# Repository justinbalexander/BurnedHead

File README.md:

# BurnedHead

A handheld, portable video game system designed with Kicad and programmed in C.

# Description

The processor is the STM32F767ZG, a Cortex-M7 processor selected for the ample
size of the instruction and data caches.  Currently at the board bring-up stage,
the functionality includes an RGB parallel interface, an MMC card socket, a 32MB
SDRAM clocked at 108MHz, D-pad, 4 front facing buttons, 2 shoulder buttons, 2
joysticks, and a speaker. The device is powered through a Micro-USB connector or
a rechargeable LiPo battery for portability.

The final product will load user-selectable ELF files off of the MMC compatible
card into the external RAM and run them as a process.

The project originally began in Zig but is transitioning to C to reduce
friction when integrating with libraries and vendor code and to allow progress
without requiring fiddling with a language still in beta.

# Building

## Cloning the Repository

This repository uses submodules to manage dependencies.

```bash
git clone --recurse-submodules https://github.com/vegecode/BurnedHead.git
```

## Building the Application

BurnedHead uses Makefiles.
Navigate to the base directory of the clone, and
point to the specific Makefile you want to build (currently only one):

Example:

```bash
make -f configurations/${CONFIGURATION_NAME}/Makefile
```

The resulting executable(s) are in `./build/${CONFIGURATION_NAME}`

# Debugging on the Target

Debugging is done using GDB in a shell with the JLink GDBServer providing the
connection to the remote target.

Running the shell script `./debug/start_debug /path/to/elf_file` will start the
GDBServer and connect GDB to it, then a gdb script loads the executable and sets
a temporary breakpoint at the reset handler.

A sample of some external RAM tests during board bring-up in a Vim/GDB session:

Another easy alternative if you are using a JLink debug probe is to use Ozone,
the standalone debugger from Segger or Segger Embedded Workbench which are
both free to use for non-commercial purposes.

Integrating with Eclipse should also be possible using the MCU GNU Eclipse
plugins.

# Hand-Assembled Revision 0 Board

The back of the first revision of the board was assembled using solder paste and
a cast-iron skillet over a stand-alone burner for reflow. Some rework was
required as applying the paste without a stencil resulted in uneven application.
The front side components were hand soldered.

# Renders

# Attributions

Some symbols and footprints  came from www.snapeda.com. See the library folder for the required
license and attributions.

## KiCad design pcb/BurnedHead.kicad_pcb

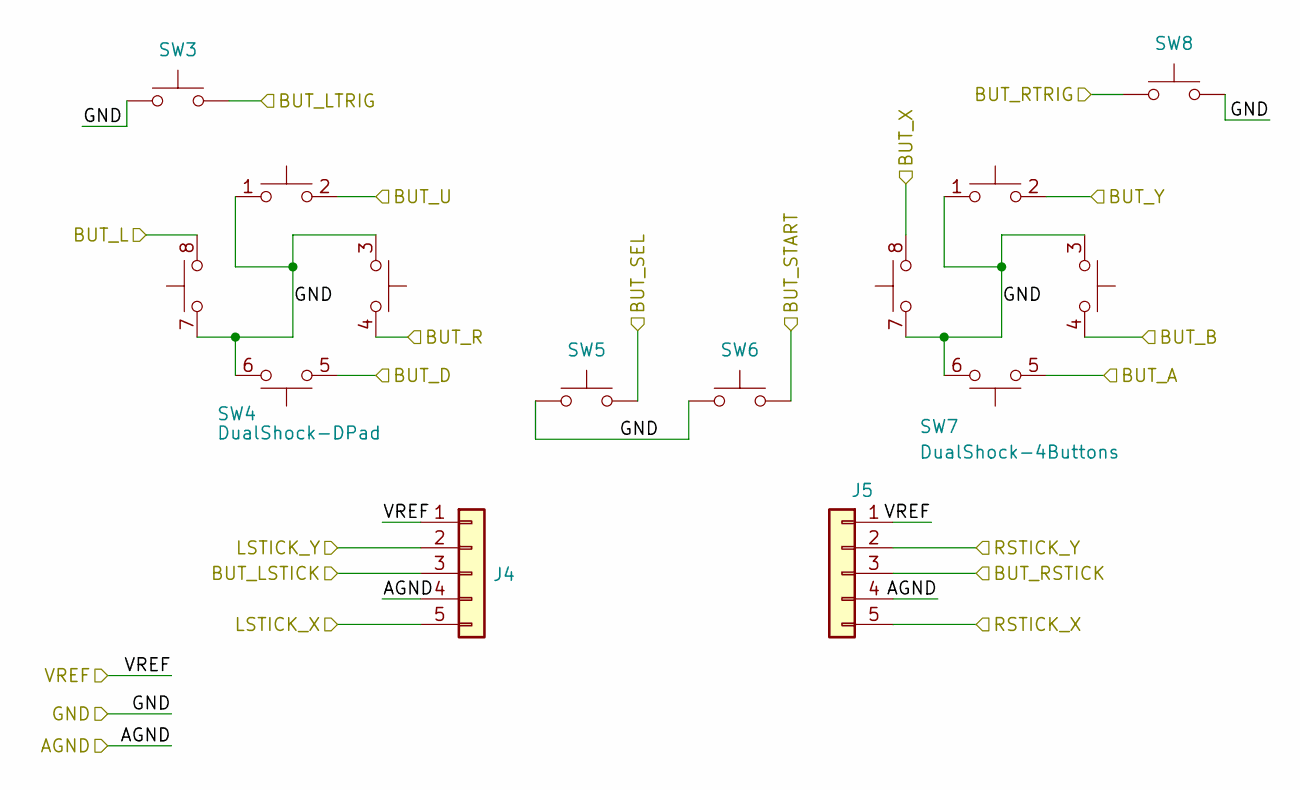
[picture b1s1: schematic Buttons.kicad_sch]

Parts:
J4, J5: FPC_1x5_TopContact_P=0.5mm; XKB-Enterprise_X05B20U05T_1x05_P0.50mm_Horizontal; Part No. X05B20U05T
SW3, SW8: SW_Push; Panasonic_EVQPUL_EVQPUC; Part No. C79175
SW4: DualShock-DPad; PS4-DualShock-CarbonPad-DPad
SW5, SW6: SW_Push; SW_SPST_PTS645
SW7: DualShock-4Buttons; PS4-DualShock-CarbonPad-4Buttons

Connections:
/Buttons/BUT_A: SW7.5; also elsewhere on the board
/Buttons/BUT_B: SW7.4; also elsewhere on the board
/Buttons/BUT_D: SW4.5; also elsewhere on the board
/Buttons/BUT_L: SW4.8; also elsewhere on the board
/Buttons/BUT_LSTICK: J4.3; also elsewhere on the board
/Buttons/BUT_LTRIG: SW3.2; also elsewhere on the board
/Buttons/BUT_R: SW4.4; also elsewhere on the board
/Buttons/BUT_RSTICK: J5.3; also elsewhere on the board
/Buttons/BUT_RTRIG: SW8.2; also elsewhere on the board
/Buttons/BUT_SEL: SW5.2; also elsewhere on the board
/Buttons/BUT_START: SW6.2; also elsewhere on the board
/Buttons/BUT_U: SW4.2; also elsewhere on the board
/Buttons/BUT_X: SW7.8; also elsewhere on the board
/Buttons/BUT_Y: SW7.2; also elsewhere on the board
/MCU/LEFT_STICK_X: J4.5; also elsewhere on the board
/MCU/LEFT_STICK_Y: J4.2; also elsewhere on the board
/MCU/RIGHT_STICK_X: J5.5; also elsewhere on the board
/MCU/RIGHT_STICK_Y: J5.2; also elsewhere on the board
/VDD: J4.1, J5.1; also elsewhere on the board
GNDD: J4.4, J5.4, SW3.1, SW4.1, SW4.3, SW4.6, SW4.7, SW5.1, SW6.1, SW7.1, SW7.3, SW7.6, SW7.7, SW8.1; also elsewhere on the board

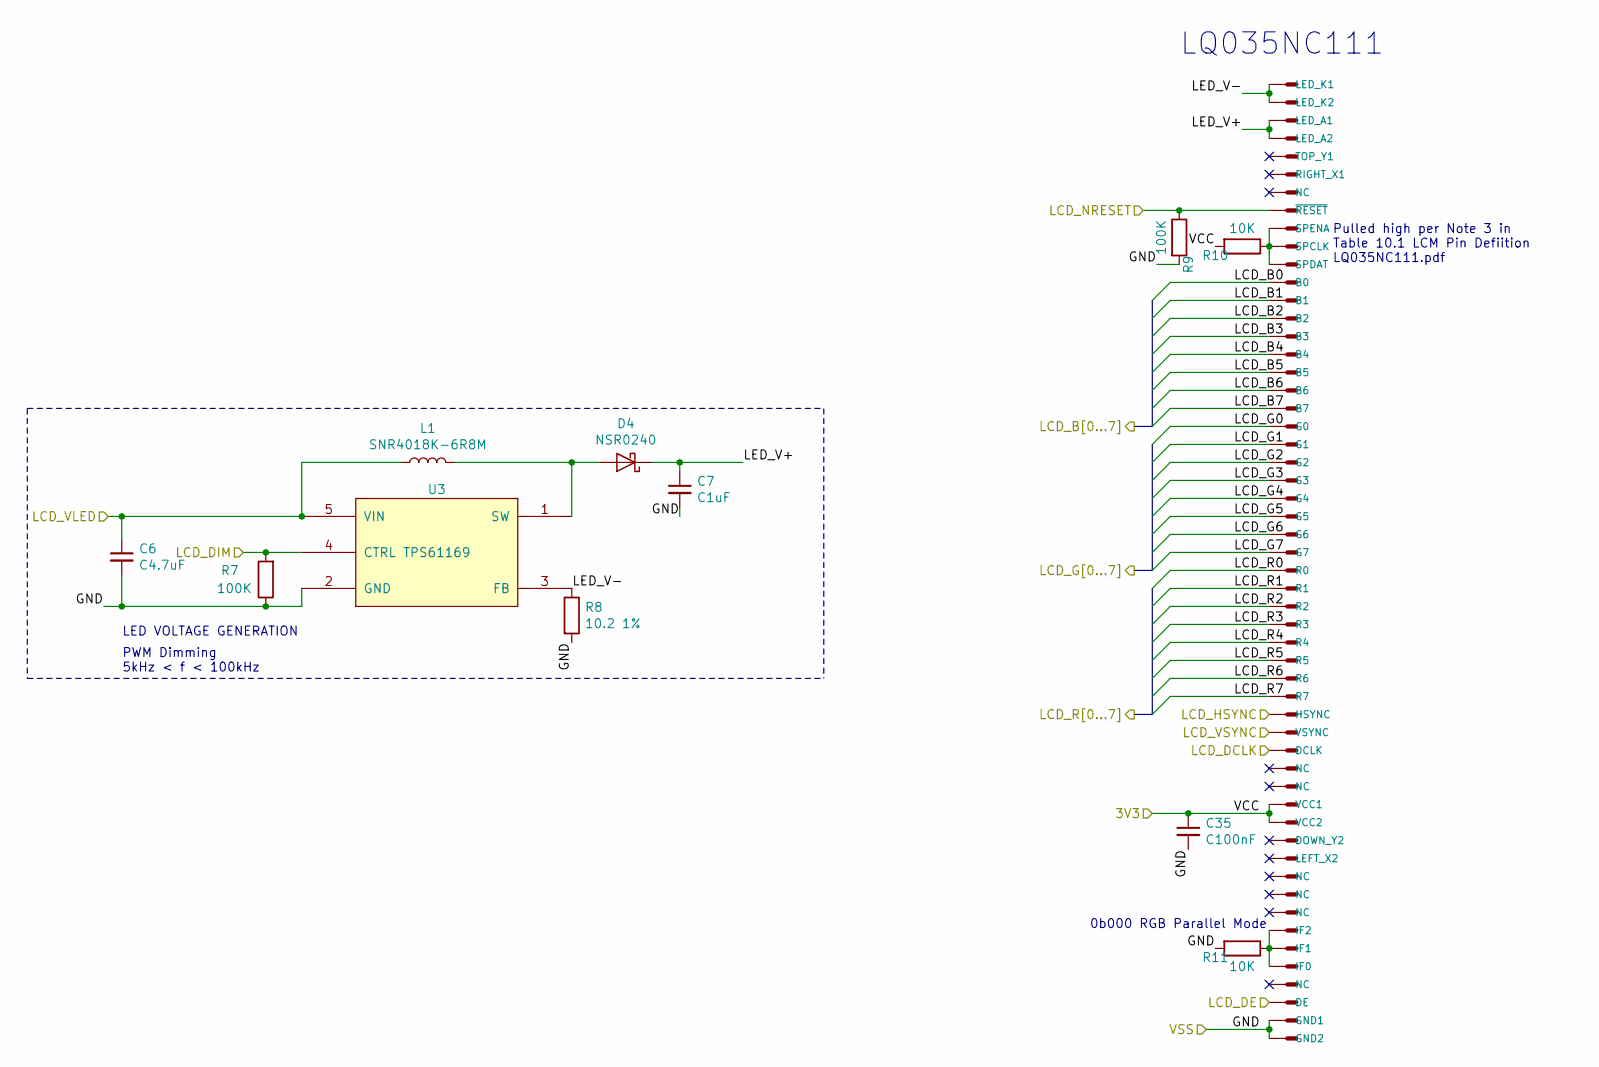
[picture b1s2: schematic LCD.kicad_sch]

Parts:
C6: C4.7uF; C_0805_2012Metric; Part No. CC0805KKX5R8BB475
C7: C1uF; C_0603_1608Metric; Part No. CC0603KRX7R7BB105
C35: C100nF; C_0603_1608Metric; Part No. AC0603KRX7R9BB104
D4: NSR0240; D_SOD-323; Part No. NSR0240HT1G
L1: SNR4018K-6R8M; L_Taiyo-Yuden_NR-40xx; Part No. SNR4018K-6R8M
R7, R9: 100K; R_0603_1608Metric
R8: 10.2 1%; R_0603_1608Metric
R10, R11: 10K; R_0603_1608Metric
U3: TPS61169; SOT-353_SC-70-5; Part No. TPS61169
U4: 51296-5494; 51296

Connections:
/LCD/LCD_B0: U4.12 (B0), U4.13 (B1), U4.14 (B2); also elsewhere on the board
/LCD/LCD_B3: U4.15 (B3); also elsewhere on the board
/LCD/LCD_B4: U4.16 (B4); also elsewhere on the board
/LCD/LCD_B5: U4.17 (B5); also elsewhere on the board
/LCD/LCD_B6: U4.18 (B6); also elsewhere on the board
/LCD/LCD_B7: U4.19 (B7); also elsewhere on the board
/LCD/LCD_DE: U4.52 (DE); also elsewhere on the board
/LCD/LCD_DIM: R7.2, U3.4 (CTRL); also elsewhere on the board
/LCD/LCD_G0: U4.20 (G0), U4.21 (G1); also elsewhere on the board
/LCD/LCD_G2: U4.22 (G2); also elsewhere on the board
/LCD/LCD_G3: U4.23 (G3); also elsewhere on the board
/LCD/LCD_G4: U4.24 (G4); also elsewhere on the board
/LCD/LCD_G5: U4.25 (G5); also elsewhere on the board
/LCD/LCD_G6: U4.26 (G6); also elsewhere on the board
/LCD/LCD_G7: U4.27 (G7); also elsewhere on the board
/LCD/LCD_HSYNC: U4.36 (HSYNC); also elsewhere on the board
/LCD/LCD_NRESET: R9.1, U4.8 (~RESET); also elsewhere on the board
/LCD/LCD_R0: U4.28 (R0), U4.29 (R1), U4.30 (R2); also elsewhere on the board
/LCD/LCD_R3: U4.31 (R3); also elsewhere on the board
/LCD/LCD_R4: U4.32 (R4); also elsewhere on the board
/LCD/LCD_R5: U4.33 (R5); also elsewhere on the board
/LCD/LCD_R6: U4.34 (R6); also elsewhere on the board
/LCD/LCD_R7: U4.35 (R7); also elsewhere on the board
/LCD/LCD_VLED: C6.1, L1.1, U3.5 (VIN); also elsewhere on the board
/LCD/LCD_VSYNC: U4.37 (VSYNC); also elsewhere on the board
/LCD/LED_V+: C7.1, D4.1 (K), U4.3 (LED_A1), U4.4 (LED_A2)
/LCD/LED_V-: R8.1, U3.3 (FB), U4.1 (LED_K1), U4.2 (LED_K2)
/MCU/LCD_CLK: U4.38 (DCLK); also elsewhere on the board
/VDD: C35.1, R10.2, U4.41 (VCC1), U4.42 (VCC2); also elsewhere on the board
GNDD: C6.2, C7.2, C35.2, R7.1, R8.2, R9.2, R11.2, U3.2 (GND), U4.53 (GND1), U4.54 (GND2); also elsewhere on the board
unnamed: D4.2 (A), L1.2, U3.1 (SW)
unnamed: R10.1, U4.9 (SPENA), U4.10 (SPCLK), U4.11 (SPDAT)
unnamed: R11.1, U4.48 (IF2), U4.49 (IF1), U4.50 (IF0)

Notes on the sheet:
LED VOLTAGE GENERATION
PWM Dimming 5kHz < f < 100kHz
0b000 RGB Parallel Mode
LQ035NC111
Pulled high per Note 3 in Table 10.1 LCM Pin Defiition LQ035NC111.pdf

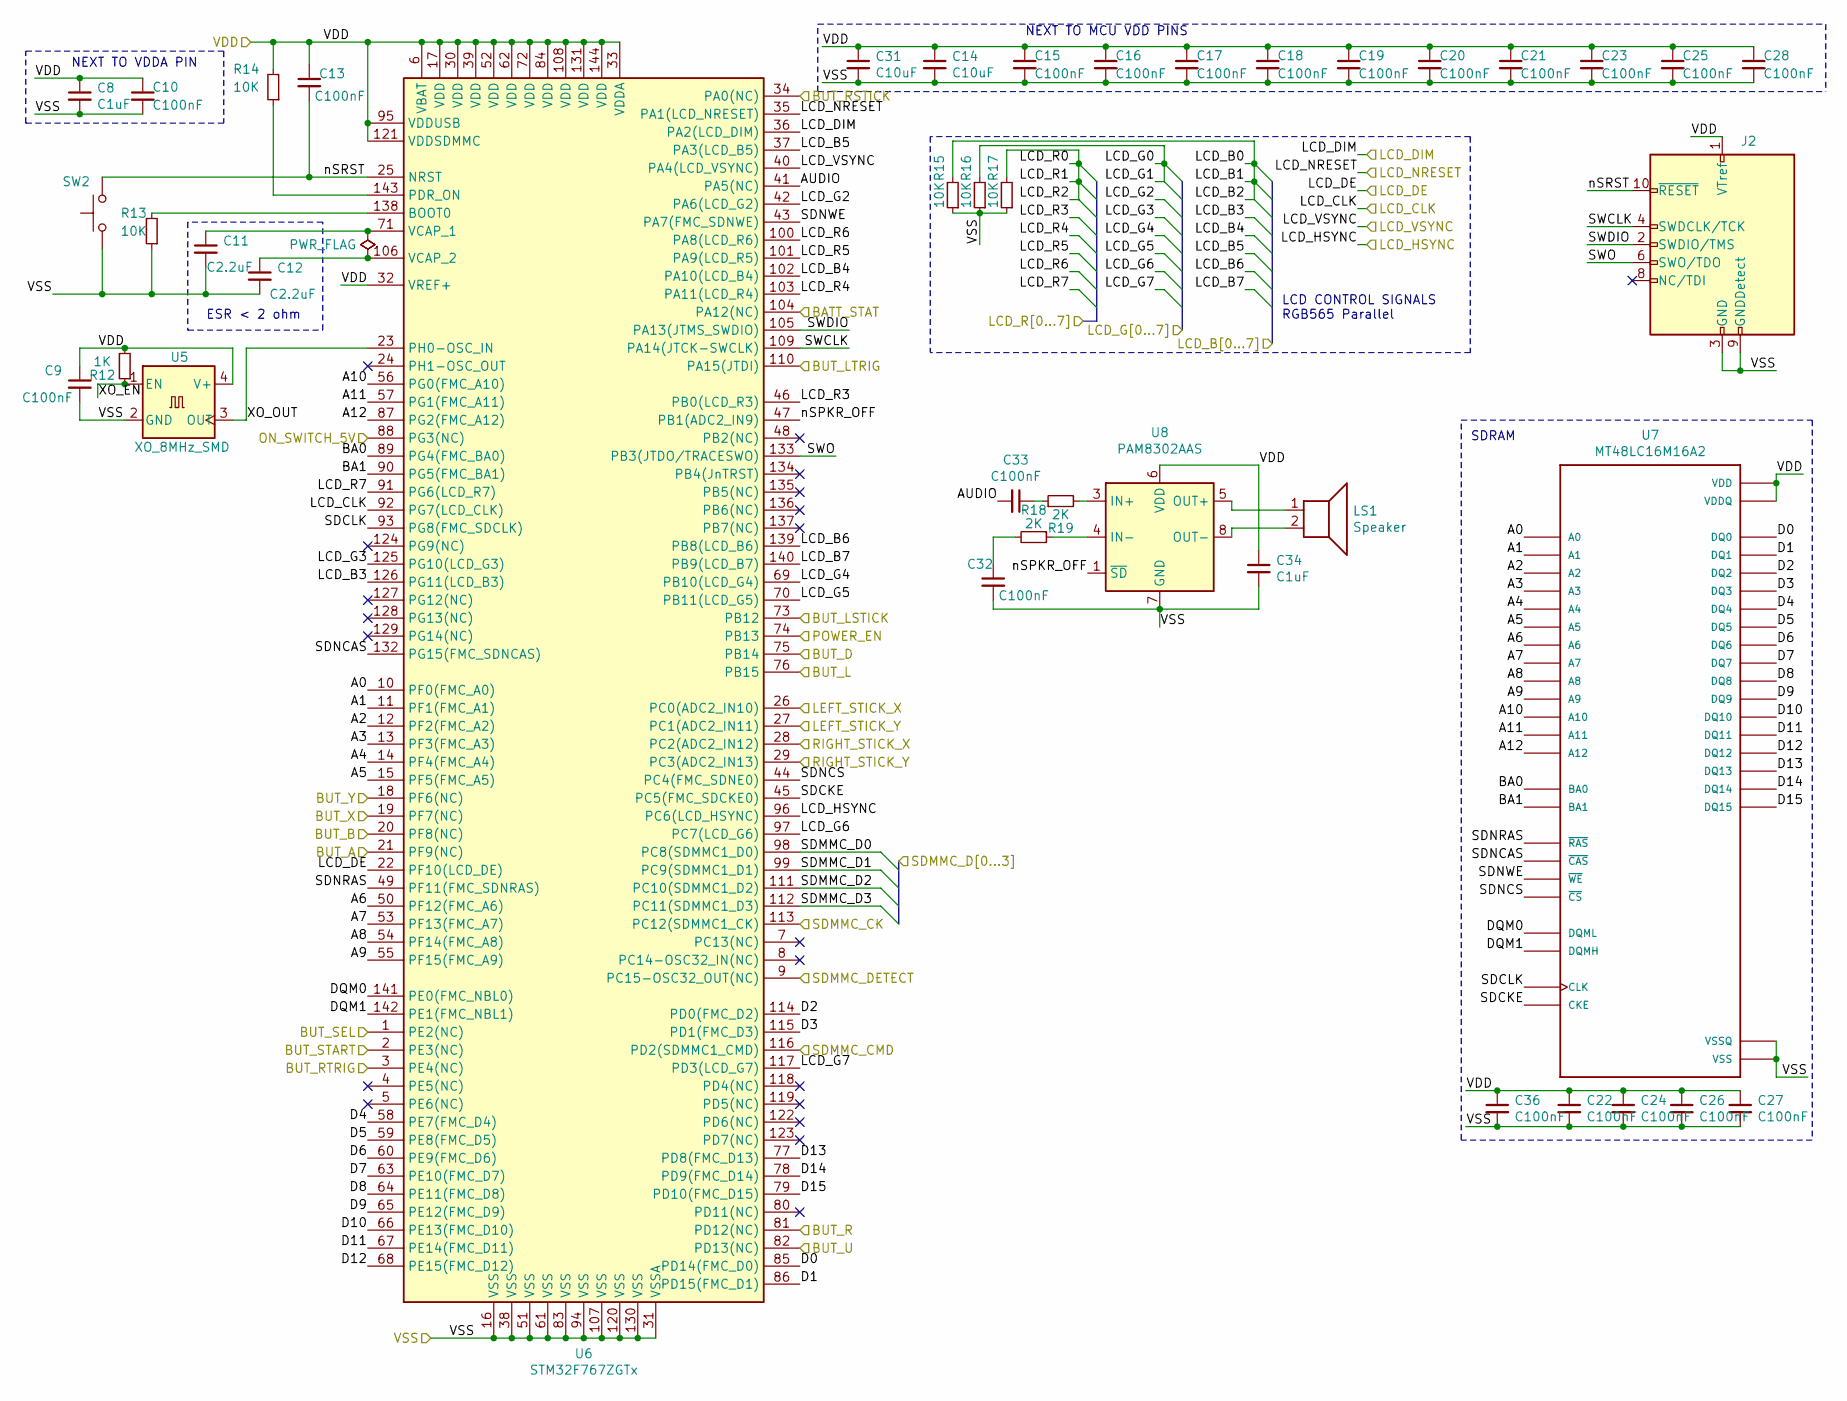
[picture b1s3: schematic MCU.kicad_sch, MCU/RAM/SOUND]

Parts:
C8: C1uF; C_0603_1608Metric; Part No. CC0603KRX7R7BB105
C9, C10, C13, C15, C16, C17, C18, C19, C20, C21, C22, C23, C24, C25, C26, C27, C28, C32, C33, C36: C100nF; C_0603_1608Metric; Part No. AC0603KRX7R9BB104
C11, C12: C2.2uF; C_0603_1608Metric; Part No. CC0603KRX5R7BB225
C14, C31: C10uF; C_1206_3216Metric; Part No. CC1206ZKY5V8BB106
C34: C1uF; C_0603_1608Metric; Part No. VJ0603G105KXJCW1BC
J2: Conn_ARM_JTAG_SWD_10; PinHeader_2x05_P1.27mm_Vertical_SMD
LS1: Speaker; PinHeader_1x02_P2.54mm_Vertical
R12: 1K; R_0603_1608Metric
R13, R14, R15, R16, R17: 10K; R_0603_1608Metric
R18, R19: 2K; R_0603_1608Metric
SW2: SW_Push; SW_SPST_PTS645
U5: XO_8MHz_SMD; Crystal_SMD_3225-4Pin_3.2x2.5mm; Part No. SiT8008AI-22-33E-8.000000D
U6: STM32F767ZGTx; LQFP-144_20x20mm_P0.5mm
U7: MT48LC16M16A2; MT48LC16M16A2TG-6A_IT; Part No. MT48LC16M16A2P-6A-IT-G; LCSC Part No. C26393
U8: PAM8302AAS; MSOP-8_3x3mm_P0.65mm

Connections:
/Buttons/BUT_A: U6.21 (PF9(NC)); also elsewhere on the board
/Buttons/BUT_B: U6.20 (PF8(NC)); also elsewhere on the board
/Buttons/BUT_D: U6.75 (PB14); also elsewhere on the board
/Buttons/BUT_L: U6.76 (PB15); also elsewhere on the board
/Buttons/BUT_LSTICK: U6.73 (PB12); also elsewhere on the board
/Buttons/BUT_LTRIG: U6.110 (PA15(JTDI)); also elsewhere on the board
/Buttons/BUT_R: U6.81 (PD12(NC)); also elsewhere on the board
/Buttons/BUT_RSTICK: U6.34 (PA0(NC)); also elsewhere on the board
/Buttons/BUT_RTRIG: U6.3 (PE4(NC)); also elsewhere on the board
/Buttons/BUT_SEL: U6.1 (PE2(NC)); also elsewhere on the board
/Buttons/BUT_START: U6.2 (PE3(NC)); also elsewhere on the board
/Buttons/BUT_U: U6.82 (PD13(NC)); also elsewhere on the board
/Buttons/BUT_X: U6.19 (PF7(NC)); also elsewhere on the board
/Buttons/BUT_Y: U6.18 (PF6(NC)); also elsewhere on the board
/LCD/LCD_B0: R15.2; also elsewhere on the board
/LCD/LCD_B3: U6.126 (PG11(LCD_B3)); also elsewhere on the board
/LCD/LCD_B4: U6.102 (PA10(LCD_B4)); also elsewhere on the board
/LCD/LCD_B5: U6.37 (PA3(LCD_B5)); also elsewhere on the board
/LCD/LCD_B6: U6.139 (PB8(LCD_B6)); also elsewhere on the board
/LCD/LCD_B7: U6.140 (PB9(LCD_B7)); also elsewhere on the board
/LCD/LCD_DE: U6.22 (PF10(LCD_DE)); also elsewhere on the board
/LCD/LCD_DIM: U6.36 (PA2(LCD_DIM)); also elsewhere on the board
/LCD/LCD_G0: R16.2; also elsewhere on the board
/LCD/LCD_G2: U6.42 (PA6(LCD_G2)); also elsewhere on the board
/LCD/LCD_G3: U6.125 (PG10(LCD_G3)); also elsewhere on the board
/LCD/LCD_G4: U6.69 (PB10(LCD_G4)); also elsewhere on the board
/LCD/LCD_G5: U6.70 (PB11(LCD_G5)); also elsewhere on the board
/LCD/LCD_G6: U6.97 (PC7(LCD_G6)); also elsewhere on the board
/LCD/LCD_G7: U6.117 (PD3(LCD_G7)); also elsewhere on the board
/LCD/LCD_HSYNC: U6.96 (PC6(LCD_HSYNC)); also elsewhere on the board
/LCD/LCD_NRESET: U6.35 (PA1(LCD_NRESET)); also elsewhere on the board
/LCD/LCD_R0: R17.2; also elsewhere on the board
/LCD/LCD_R3: U6.46 (PB0(LCD_R3)); also elsewhere on the board
/LCD/LCD_R4: U6.103 (PA11(LCD_R4)); also elsewhere on the board
/LCD/LCD_R5: U6.101 (PA9(LCD_R5)); also elsewhere on the board
/LCD/LCD_R6: U6.100 (PA8(LCD_R6)); also elsewhere on the board
/LCD/LCD_R7: U6.91 (PG6(LCD_R7)); also elsewhere on the board
/LCD/LCD_VSYNC: U6.40 (PA4(LCD_VSYNC)); also elsewhere on the board
/MCU/A0: U6.10 (PF0(FMC_A0)), U7.23 (A0)
/MCU/A1: U6.11 (PF1(FMC_A1)), U7.24 (A1)
/MCU/A2: U6.12 (PF2(FMC_A2)), U7.25 (A2)
/MCU/A3: U6.13 (PF3(FMC_A3)), U7.26 (A3)
/MCU/A4: U6.14 (PF4(FMC_A4)), U7.29 (A4)
/MCU/A5: U6.15 (PF5(FMC_A5)), U7.30 (A5)
/MCU/A6: U6.50 (PF12(FMC_A6)), U7.31 (A6)
/MCU/A7: U6.53 (PF13(FMC_A7)), U7.32 (A7)
/MCU/A8: U6.54 (PF14(FMC_A8)), U7.33 (A8)
/MCU/A9: U6.55 (PF15(FMC_A9)), U7.34 (A9)
/MCU/A10: U6.56 (PG0(FMC_A10)), U7.22 (A10)
/MCU/A11: U6.57 (PG1(FMC_A11)), U7.35 (A11)
/MCU/A12: U6.87 (PG2(FMC_A12)), U7.36 (A12)
/MCU/AUDIO: C33.2, U6.41 (PA5(NC))
/MCU/BA0: U6.89 (PG4(FMC_BA0)), U7.20 (BA0)
/MCU/BA1: U6.90 (PG5(FMC_BA1)), U7.21 (BA1)
/MCU/BATT_STAT: U6.104 (PA12(NC)); also elsewhere on the board
/MCU/D0: U6.85 (PD14(FMC_D0)), U7.2 (DQ0)
/MCU/D1: U6.86 (PD15(FMC_D1)), U7.4 (DQ1)
/MCU/D2: U6.114 (PD0(FMC_D2)), U7.5 (DQ2)
/MCU/D3: U6.115 (PD1(FMC_D3)), U7.7 (DQ3)
/MCU/D4: U6.58 (PE7(FMC_D4)), U7.8 (DQ4)
/MCU/D5: U6.59 (PE8(FMC_D5)), U7.10 (DQ5)
/MCU/D6: U6.60 (PE9(FMC_D6)), U7.11 (DQ6)
/MCU/D7: U6.63 (PE10(FMC_D7)), U7.13 (DQ7)
/MCU/D8: U6.64 (PE11(FMC_D8)), U7.42 (DQ8)
/MCU/D9: U6.65 (PE12(FMC_D9)), U7.44 (DQ9)
/MCU/D10: U6.66 (PE13(FMC_D10)), U7.45 (DQ10)
/MCU/D11: U6.67 (PE14(FMC_D11)), U7.47 (DQ11)
/MCU/D12: U6.68 (PE15(FMC_D12)), U7.48 (DQ12)
/MCU/D13: U6.77 (PD8(FMC_D13)), U7.50 (DQ13)
/MCU/D14: U6.78 (PD9(FMC_D14)), U7.51 (DQ14)
/MCU/D15: U6.79 (PD10(FMC_D15)), U7.53 (DQ15)
/MCU/DQM0: U6.141 (PE0(FMC_NBL0)), U7.15 (DQML)
/MCU/DQM1: U6.142 (PE1(FMC_NBL1)), U7.39 (DQMH)
/MCU/LCD_CLK: U6.92 (PG7(LCD_CLK)); also elsewhere on the board
/MCU/LEFT_STICK_X: U6.26 (PC0(ADC2_IN10)); also elsewhere on the board
/MCU/LEFT_STICK_Y: U6.27 (PC1(ADC2_IN11)); also elsewhere on the board
/MCU/ON_SWITCH_5V: U6.88 (PG3(NC)); also elsewhere on the board
/MCU/POWER_EN: U6.74 (PB13); also elsewhere on the board
/MCU/RIGHT_STICK_X: U6.28 (PC2(ADC2_IN12)); also elsewhere on the board
/MCU/RIGHT_STICK_Y: U6.29 (PC3(ADC2_IN13)); also elsewhere on the board
/MCU/SDCKE: U6.45 (PC5(FMC_SDCKE0)), U7.37 (CKE)
/MCU/SDCLK: U6.93 (PG8(FMC_SDCLK)), U7.38 (CLK)
/MCU/SDMMC_CK: U6.113 (PC12(SDMMC1_CK)); also elsewhere on the board
/MCU/SDMMC_CMD: U6.116 (PD2(SDMMC1_CMD)); also elsewhere on the board
/MCU/SDMMC_D0: U6.98 (PC8(SDMMC1_D0)); also elsewhere on the board
/MCU/SDMMC_D1: U6.99 (PC9(SDMMC1_D1)); also elsewhere on the board
/MCU/SDMMC_D2: U6.111 (PC10(SDMMC1_D2)); also elsewhere on the board
/MCU/SDMMC_D3: U6.112 (PC11(SDMMC1_D3)); also elsewhere on the board
/MCU/SDMMC_DETECT: U6.9 (PC15-OSC32_OUT(NC)); also elsewhere on the board
/MCU/SDNCAS: U6.132 (PG15(FMC_SDNCAS)), U7.17 (~CAS)
/MCU/SDNCS: U6.44 (PC4(FMC_SDNE0)), U7.19 (~CS)
/MCU/SDNRAS: U6.49 (PF11(FMC_SDNRAS)), U7.18 (~RAS)
/MCU/SDNWE: U6.43 (PA7(FMC_SDNWE)), U7.16 (~WE)
/MCU/SWCLK: J2.4 (SWDCLK/TCK), U6.109 (PA14(JTCK-SWCLK))
/MCU/SWDIO: J2.2 (SWDIO/TMS), U6.105 (PA13(JTMS_SWDIO))
/MCU/SWO: J2.6 (SWO/TDO), U6.133 (PB3(JTDO/TRACESWO))
/MCU/XO_EN: R12.1, U5.1 (EN)
/MCU/XO_OUT: U5.3 (OUT), U6.23 (PH0-OSC_IN)
/MCU/nSPKR_OFF: U6.47 (PB1(ADC2_IN9)), U8.1 (~SD)
/MCU/nSRST: C13.2, J2.10 (~RESET), SW2.2, U6.25 (NRST)
/VDD: C8.1, C9.1, C10.1, C13.1, C14.1, C15.1, C16.1, C17.1, C18.1, C19.1, C20.1, C21.1, C22.1, C23.1, C24.1, C25.1, C26.1, C27.1, C28.1, C31.1, C34.1, C36.1, J2.1 (VTref), R12.2, R14.2, U5.4 (V+), U6.6 (VBAT), U6.17 (VDD), U6.30 (VDD), U6.32 (VREF+), U6.33 (VDDA), U6.39 (VDD), U6.52 (VDD), U6.62 (VDD), U6.72 (VDD), U6.84 (VDD), U6.95 (VDDUSB), U6.108 (VDD), U6.121 (VDDSDMMC), U6.131 (VDD), U6.144 (VDD), U7.1 (VDD), U7.3 (VDDQ), U7.9 (VDDQ), U7.14 (VDD), U7.27 (VDD), U7.43 (VDDQ), U7.49 (VDDQ), U8.6 (VDD); also elsewhere on the board
GNDD: C8.2, C9.2, C10.2, C11.2, C12.2, C14.2, C15.2, C16.2, C17.2, C18.2, C19.2, C20.2, C21.2, C22.2, C23.2, C24.2, C25.2, C26.2, C27.2, C28.2, C31.2, C32.2, C34.2, C36.2, J2.3 (GND), J2.5 (GND), J2.9 (GNDDetect), R13.1, R15.1, R16.1, R17.1, SW2.1, U5.2 (GND), U6.16 (VSS), U6.31 (VSSA), U6.38 (VSS), U6.51 (VSS), U6.61 (VSS), U6.83 (VSS), U6.94 (VSS), U6.107 (VSS), U6.120 (VSS), U6.130 (VSS), U7.6 (VSSQ), U7.12 (VSSQ), U7.28 (VSS), U7.41 (VSS), U7.46 (VSSQ), U7.52 (VSSQ), U7.54 (VSS), U8.7 (GND); also elsewhere on the board
unnamed: C11.1, U6.71 (VCAP_1)
unnamed: C12.1, U6.106 (VCAP_2)
unnamed: C32.1, R18.2
unnamed: C33.1, R19.1
unnamed: LS1.1, U8.5 (OUT+)
unnamed: LS1.2, U8.8 (OUT-)
unnamed: R13.2, U6.138 (BOOT0)
unnamed: R14.1, U6.143 (PDR_ON)
unnamed: R18.1, U8.4 (IN-)
unnamed: R19.2, U8.3 (IN+)

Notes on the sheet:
NEXT TO VDDA PIN
ESR < 2 ohm
NEXT TO MCU VDD PINS
LCD CONTROL SIGNALS RGB565 Parallel
SDRAM

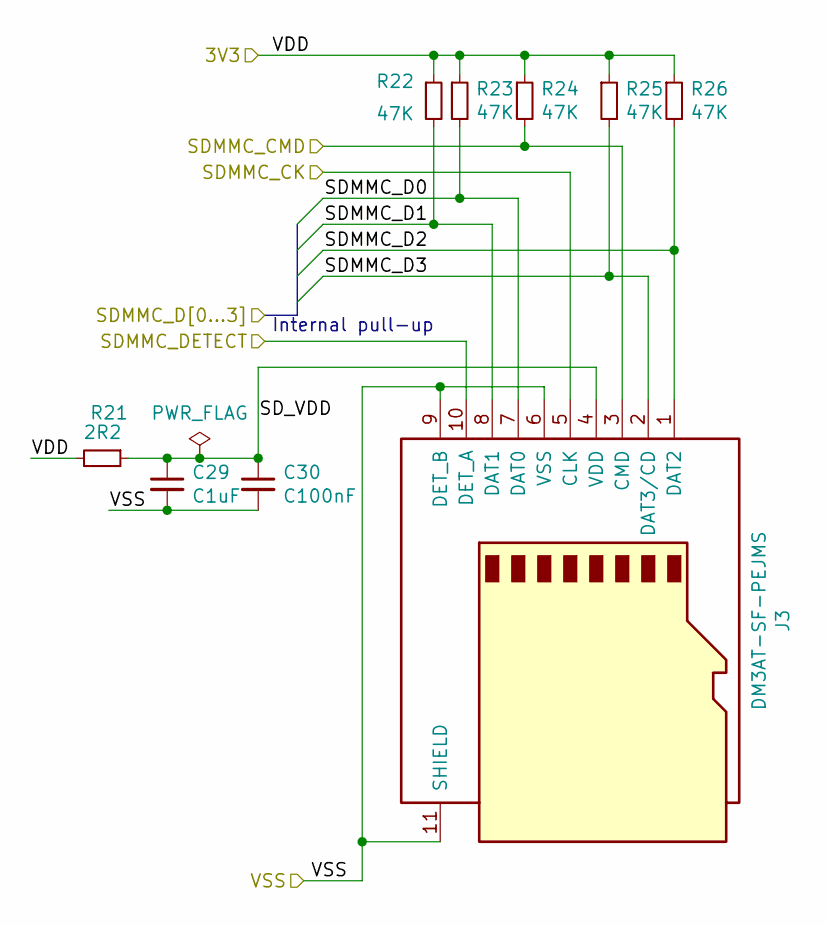
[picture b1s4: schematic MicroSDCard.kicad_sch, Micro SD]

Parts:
C29: C1uF; C_0603_1608Metric; Part No. CC0603KRX7R7BB105
C30: C100nF; C_0603_1608Metric; Part No. AC0603KRX7R9BB104
J3: DM3AT-SF-PEJMS; microSD_HC_Hirose_DM3AT-SF-PEJM5; Part No. DM3AT-SF-PEJMS
R21: 2R2; R_1206_3216Metric
R22, R23, R24, R25, R26: 47K; R_0603_1608Metric

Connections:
/MCU/SDMMC_CK: J3.5 (CLK); also elsewhere on the board
/MCU/SDMMC_CMD: J3.3 (CMD), R24.2; also elsewhere on the board
/MCU/SDMMC_D0: J3.7 (DAT0), R23.2; also elsewhere on the board
/MCU/SDMMC_D1: J3.8 (DAT1), R22.2; also elsewhere on the board
/MCU/SDMMC_D2: J3.1 (DAT2), R26.2; also elsewhere on the board
/MCU/SDMMC_D3: J3.2 (DAT3/CD), R25.2; also elsewhere on the board
/MCU/SDMMC_DETECT: J3.10 (DET_A); also elsewhere on the board
/MicroSDCard/SD_VDD: C29.1, C30.1, J3.4 (VDD), R21.1
/VDD: R21.2, R22.1, R23.1, R24.1, R25.1, R26.1; also elsewhere on the board
GNDD: C29.2, C30.2, J3.6 (VSS), J3.9 (DET_B), J3.11 (SHIELD); also elsewhere on the board

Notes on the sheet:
Internal pull-up

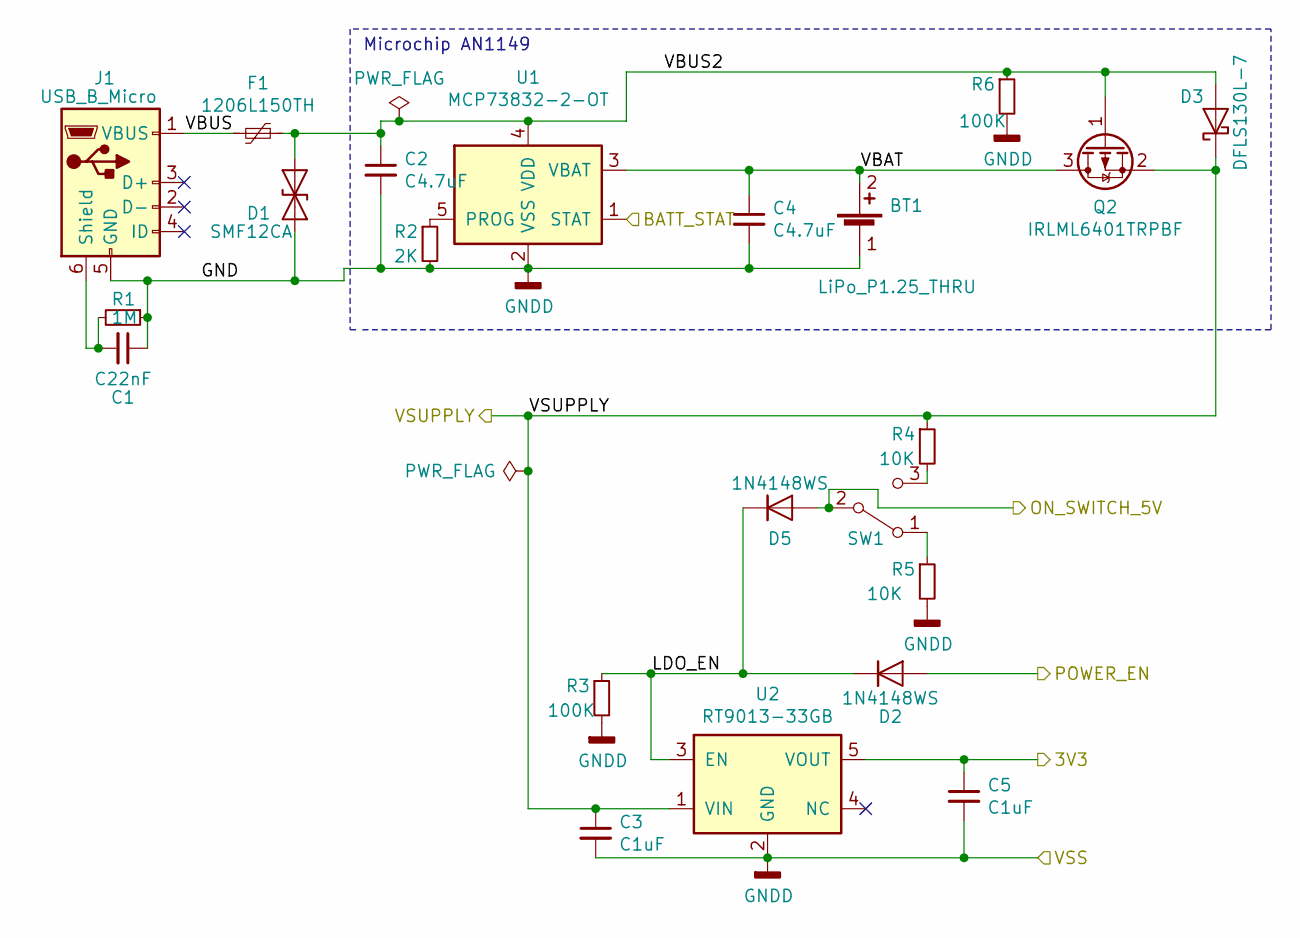
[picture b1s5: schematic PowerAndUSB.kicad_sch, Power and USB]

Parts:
BT1: LiPo_P1.25_THRU; Molex_PicoBlade_53048-0410_1x02_P1.25mm_Horizontal; Part No. A1250WR-02P
C1: C22nF; C_0603_1608Metric; Part No. CC0603KRX7R9BB223
C2, C4: C4.7uF; C_0805_2012Metric; Part No. CC0805KKX5R8BB475
C3, C5: C1uF; C_0603_1608Metric; Part No. CC0603KRX7R7BB105
D1: SMF12CA; D_SOD-123F; Part No. SMF12CA
D2, D5: 1N4148WS; D_SOD-323; Part No. 1N4148WS-7-F
D3: DFLS130L-7; D_PowerDI-123; Part No. DFLS130L-7
F1: 1206L150TH; Fuse_1206_3216Metric; Part No. 1206L150TH
J1: USB_B_Micro; USB_Micro-B_Molex_47346-0001; Part No. 47346-0001
Q2: IRLML6401TRPBF; SOT-23; Part No. IRLML6401TRPBF
R1: 1M; R_0603_1608Metric
R2: 2K; R_0603_1608Metric
R3, R6: 100K; R_0603_1608Metric
R4, R5: 10K; R_0603_1608Metric
SW1: SW_SPDT; SW_CuK_OS102011MA1QN1_SPDT_Angled; Part No. SK12D07VG4
U1: MCP73832-2-OT; SOT-23-5; Part No. MCP73832T-2ACI/OT
U2: RT9013-33GB; SOT-23-5; Part No. RT9013-33GB

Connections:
/LCD/LCD_VLED: C3.1, D3.1 (K), Q2.2 (S), R4.1, U2.1 (VIN); also elsewhere on the board
/MCU/BATT_STAT: U1.1 (STAT); also elsewhere on the board
/MCU/ON_SWITCH_5V: D5.2 (A), SW1.2 (B); also elsewhere on the board
/MCU/POWER_EN: D2.2 (A); also elsewhere on the board
/PowerAndUSB/LDO_EN: D2.1 (K), D5.1 (K), R3.1, U2.3 (EN)
/PowerAndUSB/VBAT: BT1.2 (+), C4.1, Q2.3 (D), U1.3 (VBAT)
/PowerAndUSB/VBUS: F1.2, J1.1 (VBUS)
/PowerAndUSB/VBUS2: C2.1, D1.1 (A1), D3.2 (A), F1.1, Q2.1 (G), R6.1, U1.4 (VDD)
/VDD: C5.1, U2.5 (VOUT); also elsewhere on the board
GNDD: BT1.1 (-), C1.1, C2.2, C3.2, C4.2, C5.2, D1.2 (A2), J1.5 (GND), R1.1, R2.2, R3.2, R5.2, R6.2, U1.2 (VSS), U2.2 (GND); also elsewhere on the board
unnamed: C1.2, J1.6 (Shield), R1.2
unnamed: R2.1, U1.5 (PROG)
unnamed: R4.2, SW1.3 (C)
unnamed: R5.1, SW1.1 (A)

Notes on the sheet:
Microchip AN1149

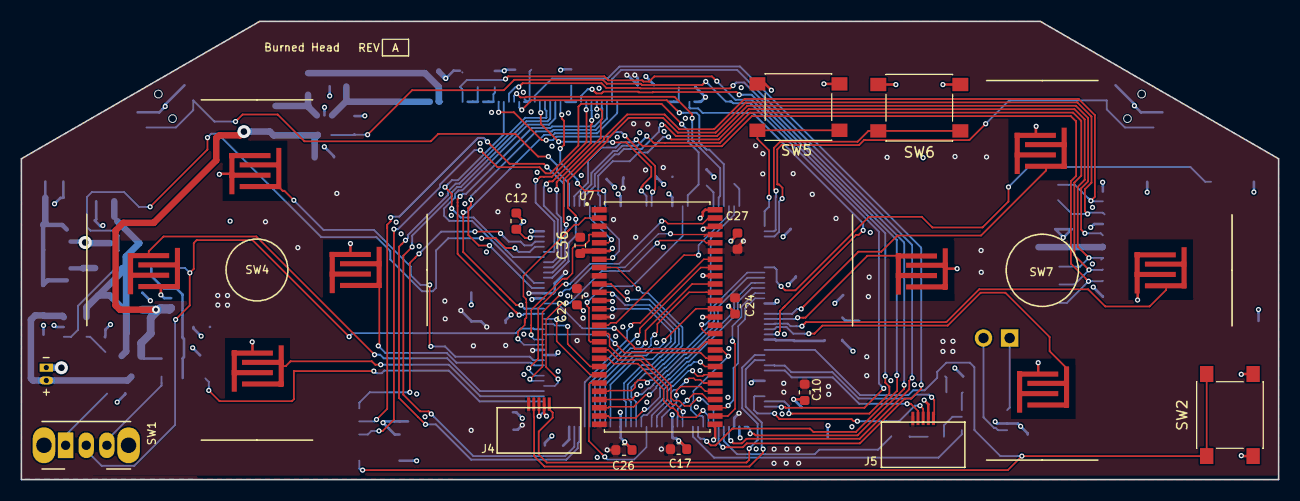
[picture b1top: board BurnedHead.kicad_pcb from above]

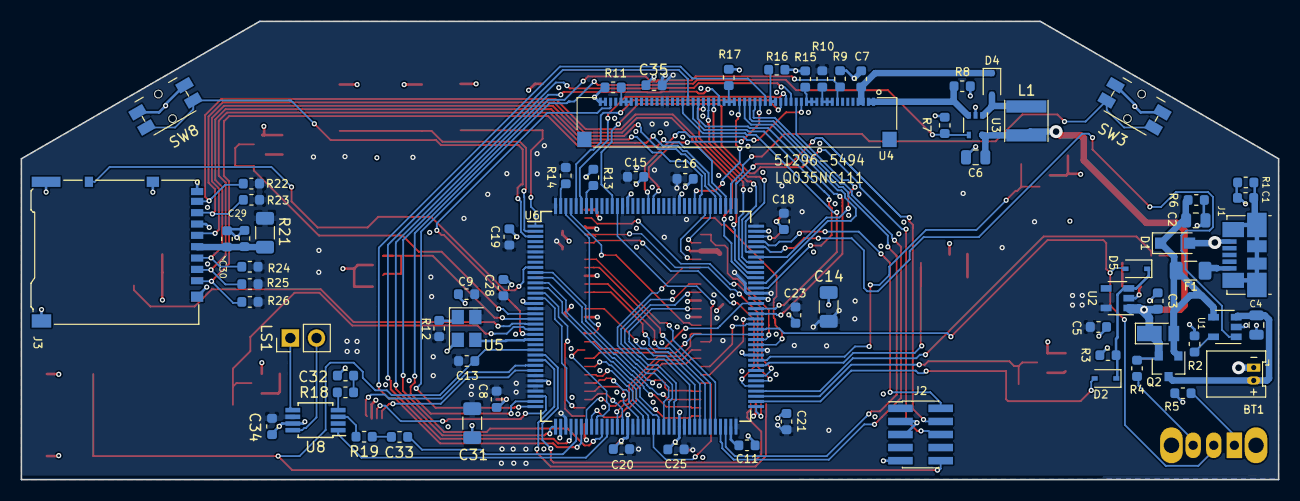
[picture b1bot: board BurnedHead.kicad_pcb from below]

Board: 4 copper layers, 121.9 x 44.4 mm, 92 parts (75 on the bottom side), 127 nets.

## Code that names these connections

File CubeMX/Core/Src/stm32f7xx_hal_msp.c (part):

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  
    __HAL_RCC_GPIOC_CLK_ENABLE();
    /**ADC2 GPIO Configuration    
    PC0     ------> ADC2_IN10
    PC1     ------> ADC2_IN11
    PC2     ------> ADC2_IN12
    PC3     ------> ADC2_IN13 
    */
    GPIO_InitStruct.Pin = GPIO_PIN_0|GPIO_PIN_1|GPIO_PIN_2|GPIO_PIN_3;
    GPIO_InitStruct.Mode = GPIO_MODE_ANALOG;
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    __HAL_RCC_ADC2_CLK_DISABLE();
  
    /**ADC2 GPIO Configuration    
    PC0     ------> ADC2_IN10
    PC1     ------> ADC2_IN11
    PC2     ------> ADC2_IN12
    PC3     ------> ADC2_IN13 
    */
    HAL_GPIO_DeInit(GPIOC, GPIO_PIN_0|GPIO_PIN_1|GPIO_PIN_2|GPIO_PIN_3);

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  
    __HAL_RCC_GPIOA_CLK_ENABLE();
    /**DAC GPIO Configuration    
    PA5     ------> DAC_OUT2 
    */
    GPIO_InitStruct.Pin = GPIO_PIN_5;
    GPIO_InitStruct.Mode = GPIO_MODE_ANALOG;
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    __HAL_RCC_DAC_CLK_DISABLE();
  
    /**DAC GPIO Configuration    
    PA5     ------> DAC_OUT2 
    */
    HAL_GPIO_DeInit(GPIOA, GPIO_PIN_5);

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    __HAL_RCC_GPIOC_CLK_ENABLE();
    __HAL_RCC_GPIOD_CLK_ENABLE();
    /**LTDC GPIO Configuration    
    PF10     ------> LTDC_DE
    PA3     ------> LTDC_B5
    PA4     ------> LTDC_VSYNC
    PA6     ------> LTDC_G2
    PB0     ------> LTDC_R3
    PB10     ------> LTDC_G4
    PB11     ------> LTDC_G5
    PG6     ------> LTDC_R7
    PG7     ------> LTDC_CLK
    PC6     ------> LTDC_HSYNC
    PC7     ------> LTDC_G6
    PA8     ------> LTDC_R6
    PA9     ------> LTDC_R5
    PA10     ------> LTDC_B4
    PA11     ------> LTDC_R4
    PD3     ------> LTDC_G7
    PG10     ------> LTDC_G3
    PG11     ------> LTDC_B3
    PB8     ------> LTDC_B6
    PB9     ------> LTDC_B7 
    */
    GPIO_InitStruct.Pin = GPIO_PIN_10;
    GPIO_InitStruct.Mode = GPIO_MODE_AF_PP;
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    __HAL_RCC_LTDC_CLK_DISABLE();
  
    /**LTDC GPIO Configuration    
    PF10     ------> LTDC_DE
    PA3     ------> LTDC_B5
    PA4     ------> LTDC_VSYNC
    PA6     ------> LTDC_G2
    PB0     ------> LTDC_R3
    PB10     ------> LTDC_G4
    PB11     ------> LTDC_G5
    PG6     ------> LTDC_R7
    PG7     ------> LTDC_CLK
    PC6     ------> LTDC_HSYNC
    PC7     ------> LTDC_G6
    PA8     ------> LTDC_R6
    PA9     ------> LTDC_R5
    PA10     ------> LTDC_B4
    PA11     ------> LTDC_R4
    PD3     ------> LTDC_G7
    PG10     ------> LTDC_G3
    PG11     ------> LTDC_B3
    PB8     ------> LTDC_B6
    PB9     ------> LTDC_B7 
    */
    HAL_GPIO_DeInit(GPIOF, GPIO_PIN_10);

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    __HAL_RCC_GPIOC_CLK_ENABLE();
    __HAL_RCC_GPIOD_CLK_ENABLE();
    /**SDMMC1 GPIO Configuration    
    PC8     ------> SDMMC1_D0
    PC9     ------> SDMMC1_D1
    PC10     ------> SDMMC1_D2
    PC11     ------> SDMMC1_D3
    PC12     ------> SDMMC1_CK
    PD2     ------> SDMMC1_CMD 
    */
    GPIO_InitStruct.Pin = GPIO_PIN_8|GPIO_PIN_9|GPIO_PIN_10|GPIO_PIN_11 
                          |GPIO_PIN_12;
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    __HAL_RCC_SDMMC1_CLK_DISABLE();
  
    /**SDMMC1 GPIO Configuration    
    PC8     ------> SDMMC1_D0
    PC9     ------> SDMMC1_D1
    PC10     ------> SDMMC1_D2
    PC11     ------> SDMMC1_D3
    PC12     ------> SDMMC1_CK
    PD2     ------> SDMMC1_CMD 
    */
    HAL_GPIO_DeInit(GPIOC, GPIO_PIN_8|GPIO_PIN_9|GPIO_PIN_10|GPIO_PIN_11 
                          |GPIO_PIN_12);
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  __HAL_RCC_FMC_CLK_ENABLE();
  
  /** FMC GPIO Configuration  
  PF0   ------> FMC_A0
  PF1   ------> FMC_A1
  PF2   ------> FMC_A2
  PF3   ------> FMC_A3
  PF4   ------> FMC_A4
  PF5   ------> FMC_A5
  PA7   ------> FMC_SDNWE
  PC4   ------> FMC_SDNE0
  PC5   ------> FMC_SDCKE0
  PF11   ------> FMC_SDNRAS
  PF12   ------> FMC_A6
  PF13   ------> FMC_A7
  PF14   ------> FMC_A8
  PF15   ------> FMC_A9
  PG0   ------> FMC_A10
  PG1   ------> FMC_A11
  PE7   ------> FMC_D4
  PE8   ------> FMC_D5
  PE9   ------> FMC_D6
  PE10   ------> FMC_D7
  PE11   ------> FMC_D8
  PE12   ------> FMC_D9
  PE13   ------> FMC_D10
  PE14   ------> FMC_D11
  PE15   ------> FMC_D12
  PD8   ------> FMC_D13
  PD9   ------> FMC_D14
  PD10   ------> FMC_D15
  PD14   ------> FMC_D0
  PD15   ------> FMC_D1
  PG2   ------> FMC_A12
  PG4   ------> FMC_BA0
  PG5   ------> FMC_BA1
  PG8   ------> FMC_SDCLK
  PD0   ------> FMC_D2
  PD1   ------> FMC_D3
  PG15   ------> FMC_SDNCAS
  PE0   ------> FMC_NBL0
  PE1   ------> FMC_NBL1
  */
  GPIO_InitStruct.Pin = GPIO_PIN_0|GPIO_PIN_1|GPIO_PIN_2|GPIO_PIN_3 
                          |GPIO_PIN_4|GPIO_PIN_5|GPIO_PIN_11|GPIO_PIN_12 
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  __HAL_RCC_FMC_CLK_DISABLE();
  
  /** FMC GPIO Configuration  
  PF0   ------> FMC_A0
  PF1   ------> FMC_A1
  PF2   ------> FMC_A2
  PF3   ------> FMC_A3
  PF4   ------> FMC_A4
  PF5   ------> FMC_A5
  PA7   ------> FMC_SDNWE
  PC4   ------> FMC_SDNE0
  PC5   ------> FMC_SDCKE0
  PF11   ------> FMC_SDNRAS
  PF12   ------> FMC_A6
  PF13   ------> FMC_A7
  PF14   ------> FMC_A8
  PF15   ------> FMC_A9
  PG0   ------> FMC_A10
  PG1   ------> FMC_A11
  PE7   ------> FMC_D4
  PE8   ------> FMC_D5
  PE9   ------> FMC_D6
  PE10   ------> FMC_D7
  PE11   ------> FMC_D8
  PE12   ------> FMC_D9
  PE13   ------> FMC_D10
  PE14   ------> FMC_D11
  PE15   ------> FMC_D12
  PD8   ------> FMC_D13
  PD9   ------> FMC_D14
  PD10   ------> FMC_D15
  PD14   ------> FMC_D0
  PD15   ------> FMC_D1
  PG2   ------> FMC_A12
  PG4   ------> FMC_BA0
  PG5   ------> FMC_BA1
  PG8   ------> FMC_SDCLK
  PD0   ------> FMC_D2
  PD1   ------> FMC_D3
  PG15   ------> FMC_SDNCAS
  PE0   ------> FMC_NBL0
  PE1   ------> FMC_NBL1
  */
  HAL_GPIO_DeInit(GPIOF, GPIO_PIN_0|GPIO_PIN_1|GPIO_PIN_2|GPIO_PIN_3 
                          |GPIO_PIN_4|GPIO_PIN_5|GPIO_PIN_11|GPIO_PIN_12 
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
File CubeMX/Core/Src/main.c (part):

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  /*Configure GPIO pin Output Level */
  HAL_GPIO_WritePin(GPIOB, GPIO_PIN_1, GPIO_PIN_RESET);

  /*Configure GPIO pins : PE2 PE3 PE4 */
  GPIO_InitStruct.Pin = GPIO_PIN_2|GPIO_PIN_3|GPIO_PIN_4;
  GPIO_InitStruct.Mode = GPIO_MODE_INPUT;
  GPIO_InitStruct.Pull = GPIO_NOPULL;
  HAL_GPIO_Init(GPIOE, &GPIO_InitStruct);

  /*Configure GPIO pin : PC15 */
  GPIO_InitStruct.Pin = GPIO_PIN_15;
  GPIO_InitStruct.Mode = GPIO_MODE_INPUT;
  GPIO_InitStruct.Pull = GPIO_NOPULL;
  HAL_GPIO_Init(GPIOC, &GPIO_InitStruct);

  /*Configure GPIO pins : PF6 PF7 PF8 PF9 */
  GPIO_InitStruct.Pin = GPIO_PIN_6|GPIO_PIN_7|GPIO_PIN_8|GPIO_PIN_9;
  GPIO_InitStruct.Mode = GPIO_MODE_INPUT;
  GPIO_InitStruct.Pull = GPIO_NOPULL;
  HAL_GPIO_Init(GPIOF, &GPIO_InitStruct);

  /*Configure GPIO pins : PA0 PA12 PA15 */
  GPIO_InitStruct.Pin = GPIO_PIN_0|GPIO_PIN_12|GPIO_PIN_15;
  GPIO_InitStruct.Mode = GPIO_MODE_INPUT;
  GPIO_InitStruct.Pull = GPIO_NOPULL;
  HAL_GPIO_Init(GPIOA, &GPIO_InitStruct);

  /*Configure GPIO pin : PA1 */
  GPIO_InitStruct.Pin = GPIO_PIN_1;
  GPIO_InitStruct.Mode = GPIO_MODE_OUTPUT_PP;
  GPIO_InitStruct.Pull = GPIO_NOPULL;
  GPIO_InitStruct.Speed = GPIO_SPEED_FREQ_LOW;
  HAL_GPIO_Init(GPIOA, &GPIO_InitStruct);

  /*Configure GPIO pin : PA2 */
  GPIO_InitStruct.Pin = GPIO_PIN_2;
  GPIO_InitStruct.Mode = GPIO_MODE_AF_PP;
  GPIO_InitStruct.Pull = GPIO_NOPULL;
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  GPIO_InitStruct.Alternate = GPIO_AF3_TIM9;
  HAL_GPIO_Init(GPIOA, &GPIO_InitStruct);

  /*Configure GPIO pin : PB1 */
  GPIO_InitStruct.Pin = GPIO_PIN_1;
  GPIO_InitStruct.Mode = GPIO_MODE_OUTPUT_PP;
  GPIO_InitStruct.Pull = GPIO_NOPULL;
  GPIO_InitStruct.Speed = GPIO_SPEED_FREQ_LOW;
  HAL_GPIO_Init(GPIOB, &GPIO_InitStruct);

  /*Configure GPIO pins : PB12 PB13 PB14 PB15 */
  GPIO_InitStruct.Pin = GPIO_PIN_12|GPIO_PIN_13|GPIO_PIN_14|GPIO_PIN_15;
  GPIO_InitStruct.Mode = GPIO_MODE_INPUT;
  GPIO_InitStruct.Pull = GPIO_NOPULL;
  HAL_GPIO_Init(GPIOB, &GPIO_InitStruct);

  /*Configure GPIO pins : PD12 PD13 */
  GPIO_InitStruct.Pin = GPIO_PIN_12|GPIO_PIN_13;
  GPIO_InitStruct.Mode = GPIO_MODE_INPUT;
  GPIO_InitStruct.Pull = GPIO_NOPULL;
  HAL_GPIO_Init(GPIOD, &GPIO_InitStruct);

  /*Configure GPIO pin : PG3 */
  GPIO_InitStruct.Pin = GPIO_PIN_3;
  GPIO_InitStruct.Mode = GPIO_MODE_INPUT;
  GPIO_InitStruct.Pull = GPIO_NOPULL;
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

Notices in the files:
CubeMX/Core/Src/main.c:
© Copyright (c) 2020 STMicroelectronics.
All rights reserved.
This software component is licensed by ST under BSD 3-Clause license,
the "License"; You may not use this file except in compliance with the
License. You may obtain a copy of the License at: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
(C) COPYRIGHT STMicroelectronics *****END OF FILE
